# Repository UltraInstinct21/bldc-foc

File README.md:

# bldc-foc

Sensored field-oriented control firmware for a custom 24 V BLDC drive:

- STM32G431CBT6 (170 MHz, LQFP-48)
- DRV8316CT gate driver, 6x PWM in hardware mode, integrated current sense (0.3 V/A)
- AS5600 magnetic encoder on I2C1
- 24 V outrunner, 7 pole pairs, 5 Arms, 2000 rpm
- External ESP32 WiFi bridge for browser-based telemetry and motor control

The firmware is split into independent test applications, one per board
function, plus standalone FOC and FOC + ESP32 WiFi bridge applications. Each app
links the same board layer and is flashed on its own.

## Layout

| Path | Contents |
|---|---|
| `firmware/` | Build system and STM32 source code |
| `firmware/common/` | Clock, GPIO, pin AFs, interrupts, UART console & link |
| `firmware/foc/` | Standalone FOC application (I2C encoder, automatic start) |
| `firmware/foc_esp/` | FOC application with ESP32 half-duplex UART link |
| `firmware/tests/` | Eight independent hardware test apps (`test_00` to `test_07`) |
| `firmware/Drivers/` | ST HAL and CMSIS |
| `esp32/` | Arduino sketch and web app for external ESP32 WiFi bridge |
| `hardware/` | KiCad schematic and PCB for board revision v6 |
| `docs/` | Hardware, motor, control, bring-up, and ESP32 interface documentation |

## Quick start

### STM32 firmware
Requirements: `arm-none-eabi-gcc`, OpenOCD, and an ST-Link probe.

```sh
cd firmware

make APP=test_00_hello flash    # first board check
make APP=test_07_esp_link flash # verify ESP32 link without motor
make APP=foc flash              # standalone FOC app
make APP=foc_esp flash          # FOC + ESP32 WiFi control app
make apps                       # build every app
```

Full build and flash details are in [`firmware/README.md`](firmware/README.md).

### ESP32 WiFi bridge
Flash `esp32/bldc_bridge/bldc_bridge.ino` using the Arduino IDE.
Connect to WiFi **BLDC-FOC** (password `bldcfoc123`) and open `http://192.168.4.1`.
See [`esp32/README.md`](esp32/README.md) for wiring and setup.

## Documentation

- [`docs/hardware.md`](docs/hardware.md) - board, pin map, connectors, limitations
- [`docs/motor.md`](docs/motor.md) - motor data and the constants derived from it
- [`docs/control.md`](docs/control.md) - FOC implementation, tuning, sampling window
- [`docs/bringup.md`](docs/bringup.md) - ordered test and calibration procedure
- [`docs/esp32.md`](docs/esp32.md) - ESP32 WiFi bridge protocol, timing, and safety design
- [`firmware/tests/README.md`](firmware/tests/README.md) - expected output per test
- [`firmware/foc_esp/README.md`](firmware/foc_esp/README.md) - FOC + ESP32 application details
- [`esp32/README.md`](esp32/README.md) - ESP32 Arduino build, flash, and wiring guide
- [`hardware/README.md`](hardware/README.md) - PCB files and board notes

## Current state

- Current-mode FOC at 20 kHz, angle from the AS5600.
- Standalone `foc`: ramps a fixed `iq` and guards at 800 rpm.
- WiFi-controlled `foc_esp`: commanded over half-duplex UART at 230400 baud with dual watchdogs.
- The AS5600 is a bring-up sensor (about 1000 rpm max). Rated speed needs an ABZ
  or SPI absolute encoder.
- The board has no Vbus sense; the 0.3 V/A CSA gain limits measurable current to ±4.6 A.

## License

MIT. See [`LICENSE`](LICENSE).

The bundled ST HAL and CMSIS sources under `firmware/Drivers/` keep their own
ST license terms; see `firmware/Drivers/CMSIS/LICENSE.txt` and the headers in
the HAL sources.

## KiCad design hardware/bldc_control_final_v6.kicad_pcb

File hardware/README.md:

# BLDC Motor Controller — Board Revision v6

KiCad sources for the 24 V three-phase BLDC drive, board revision v6
(`bldc_control_final_v6`).

| File | Contents |
|---|---|
| `bldc_control_final_v6.kicad_pro` | KiCad project |
| `bldc_control_final_v6.kicad_sch` | Single-sheet schematic |
| `bldc_control_final_v6.kicad_pcb` | 2-layer PCB |

Open the `.kicad_pro` file with KiCad 7 or newer.

## Quick facts

| Item | Value |
|---|---|
| Input voltage | 12 to 24 V DC on J1; USB-C 5 V as alternate supply |
| Motor output | Three phases on J2 (ph_C, ph_B, ph_A) |
| Gate driver | DRV8316CT, integrated FETs, 6x PWM, hardware strap configuration, no SPI |
| Current sense | Integrated CSA, 0.3 V/A, VREF = 3.3 V, linear range ±4.6 A |
| MCU | STM32G431CBT6, LQFP-48, 170 MHz, 128 KB flash, 32 KB RAM |
| Power regulators | LMR36510 buck (24 V → 5 V), TPS2116 mux, TPS7A4533 LDO (5 V → 3.3 V) |
| Encoder interface | I2C1 on PA15 (SCL) and PB7 (SDA), J6 / J7 |
| Debug / link | USART1 on J7 (PB6 TX, PB7 RX) |
| Programming | SWD on J5 |
| PCB | 2-layer, Rev v6 |

## Connectors

| Connector | Pins | Signal | Description |
|---|---|---|---|
| J1 | 2 | 12–24 V / GND | Motor supply input |
| J2 | 3 | ph_C / ph_B / ph_A | Motor phase outputs |
| J3 | — | USB-C | 5 V backup supply and USB data (see errata) |
| J5 | 4 | 3V3 / SWDIO / SWCLK / GND | SWD debug header |
| J6 | 3 | 3V3 / OUT (PA15) / GND | Encoder supply and SCL; also OUT pin |
| J7 | 2 | PB6 (USART1_TX) / PB7 (USART1_RX) | UART console and ESP32 link |

J7 has no ground pin. Use J5 pin 4 or J6 pin 3 as the signal ground.
J6 pin 2 connects to PA15, which carries I2C1_SCL (AF4) for the AS5600.

## Power tree

```
12–24 V input (J1)
    └── F1 PTC fuse
        └── LMR36510 buck  →  5 V
                               └── TPS2116 mux  ←  USB-C 5 V (J3)
                                       └── TPS7A4533 LDO  →  3.3 V
```

The DRV8316CT runs directly from the protected input rail. The STM32 and all
logic run from the 3.3 V LDO output.

## DRV8316CT hardware straps

The DRV8316CT is configured entirely by pin straps. There is no SPI connection
to the driver; the firmware only drives nSLEEP and DRVOFF and reads nFAULT.

| Pin | Strap | Setting | Result |
|---|---|---|---|
| MODE | AGND | — | 6x PWM mode, SOA/SOB/SOC outputs active |
| GAIN | Hi-Z | — | CSA gain 0.3 V/A |
| SLEW | 47 kΩ to AVDD | — | Gate slew rate 125 V/µs |
| OCP/SR | Hi-Z | — | OCP threshold 16 A, active demagnetization |
| VREF/ILIM | 3V3 | — | 1.65 V mid-rail offset, ±4.6 A linear CSA range |

## Known deviations and errata

| # | Item | Impact |
|---|---|---|
| 1 | USB-C CC pull-ups are connected to 3.3 V instead of 5.1 kΩ to GND | USB-C power negotiation fails; the board accepts 5 V but cannot negotiate higher current from a compliant charger |
| 2 | F1 PTC fuse is rated 16 V; input may reach 24 V | The fuse may trip at high current on a 24 V supply; verify thermal behaviour before sustained 24 V operation |
| 3 | SW4 connects NRST to 3.3 V instead of GND | Pressing SW4 has no effect; use the OpenOCD `reset` command or the SWD reset line to reset the MCU |
| 4 | BOOT0 is unconnected; it floats to logic 0 via the internal pull-down | The MCU always boots from flash; DFU mode via BOOT0 is not accessible without a hardware rework |
| 5 | DRV8316CT internal buck (SW_BK / FB_BK) is unused | Only an RC network is fitted; the internal buck is disabled. No functional impact |
| 6 | PB10 and PB11 are labelled I2C1_SCL / I2C1_SDA on the schematic | PB10/PB11 have no I2C1 alternate function on the STM32G431CB. The pads are unconnected on the board; do not use them for the encoder |
| 7 | CSA linear range is ±4.6 A; rated motor current is 7 A | Full motor torque cannot be measured accurately. Keep peak iq ≤ 4.0 A in firmware to stay within the measurement window |
| 8 | SLEW strap gives 125 V/µs (not 200 V/µs) | Dead-time margin is slightly reduced relative to the datasheet default. Keep `FOC_VMAX_FRAC` ≤ 0.45 in firmware |

## Firmware

The firmware build system and all source code are in `firmware/`. See
`../firmware/README.md` for build instructions, the application list, and
toolchain requirements.

The `foc_esp` application adds a half-duplex UART link to an external ESP32
WiFi bridge. See `../firmware/foc_esp/README.md` and `../docs/esp32.md`.

## Not in this repository

Schematic and PCB PDFs, Gerbers, drill files, the BOM and the motor design
report are kept locally and are covered by `.gitignore`.

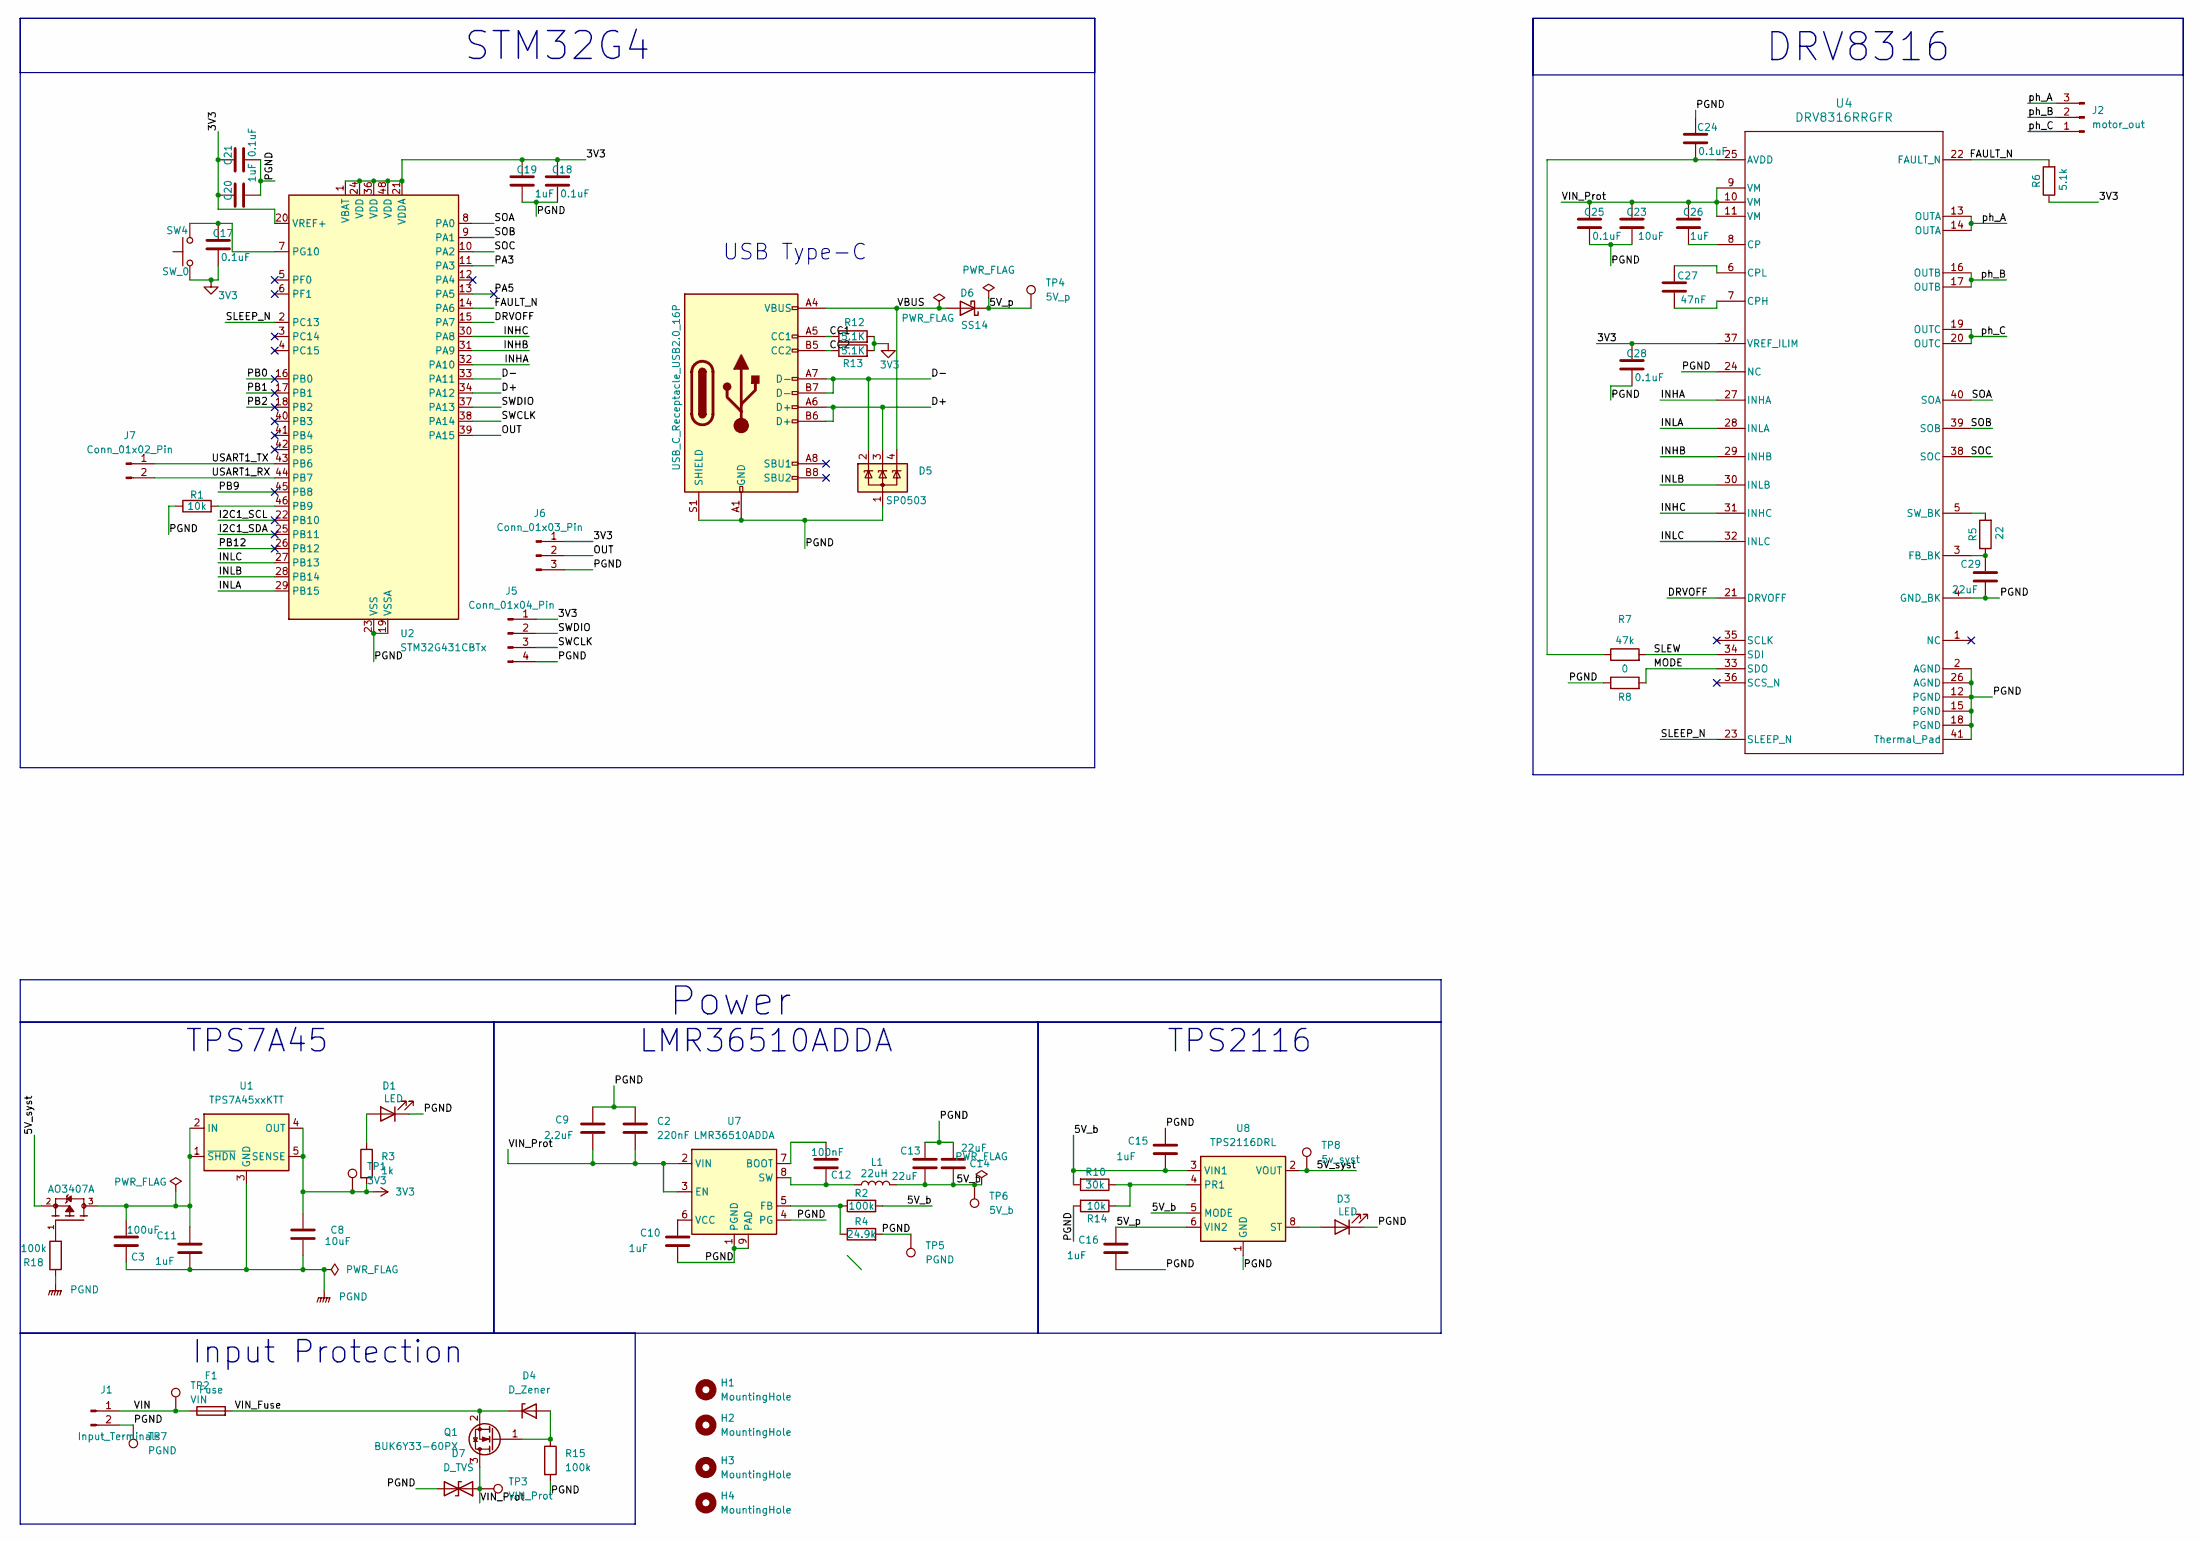
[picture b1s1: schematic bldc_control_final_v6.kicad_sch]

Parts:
C2: 220nF; C_0805_2012Metric_Pad1.18x1.45mm_HandSolder
C3: 100uF; C_0805_2012Metric_Pad1.18x1.45mm_HandSolder
C8: 10uF; C_0805_2012Metric_Pad1.18x1.45mm_HandSolder
C9: 2.2uF; C_0805_2012Metric_Pad1.18x1.45mm_HandSolder
C10, C11, C15, C16, C19, C20, C26: 1uF; C_0805_2012Metric_Pad1.18x1.45mm_HandSolder
C12: 100nF; C_0805_2012Metric_Pad1.18x1.45mm_HandSolder
C13, C14, C29: 22uF; C_1206_3216Metric_Pad1.33x1.80mm_HandSolder
C17, C18, C21, C24, C25, C28: 0.1uF; C_0805_2012Metric_Pad1.18x1.45mm_HandSolder
C23: 10uF; C_1210_3225Metric_Pad1.33x2.70mm_HandSolder
C27: 47nF; C_0805_2012Metric_Pad1.18x1.45mm_HandSolder
D1, D3: LED; LED_0603_1608Metric
D4: D_Zener; D_SOD-123
D5: SP0503; SOT-143
D6: SS14; D_SMA
D7: D_TVS; D_SMB_Handsoldering
F1: Fuse; Fuse_Bourns_MF-RHT500
H1, H2, H3, H4: MountingHole; MountingHole_2.2mm_M2
J1: Input_Terminals; TerminalBlock_Phoenix_PT-1,5-2-5.0-H_1x02_P5.00mm_Horizontal
J2: motor_out; TerminalBlock_Phoenix_PT-1,5-3-5.0-H_1x03_P5.00mm_Horizontal
J3: USB_C_Receptacle_USB2.0_16P; USB_C_Receptacle_GCT_USB4110
J5: Conn_01x04_Pin; PinHeader_1x04_P2.54mm_Vertical
J6: Conn_01x03_Pin; PinHeader_1x03_P2.54mm_Vertical
J7: Conn_01x02_Pin; PinHeader_1x02_P2.54mm_Vertical
L1: 22uH; L_Bourns-SRN6028
Q1: BUK6Y33-60PX; LFPAK56
Q2: AO3407A; SOT-23; PARTREV 5
R1, R14: 10k; R_0805_2012Metric_Pad1.20x1.40mm_HandSolder
R2, R15, R18: 100k; R_0805_2012Metric_Pad1.20x1.40mm_HandSolder
R3: 1k; R_0805_2012Metric_Pad1.20x1.40mm_HandSolder
R4: 24.9k; R_0805_2012Metric_Pad1.20x1.40mm_HandSolder
R5: 22; R_0805_2012Metric_Pad1.20x1.40mm_HandSolder
R6: 5.1k; R_0805_2012Metric_Pad1.20x1.40mm_HandSolder
R7: 47k; R_0805_2012Metric_Pad1.20x1.40mm_HandSolder
R8: 0; R_0805_2012Metric_Pad1.20x1.40mm_HandSolder
R10: 30k; R_0805_2012Metric_Pad1.20x1.40mm_HandSolder
R12, R13: 5.1K; R_0805_2012Metric_Pad1.20x1.40mm_HandSolder
SW4: SW_0; SW_Push_SPST_NO_Alps_SKRK
TP1: 3V3; TestPoint_Pad_1.5x1.5mm
TP2: VIN; TestPoint_Pad_1.5x1.5mm
TP3: VIN_Prot; TestPoint_Pad_1.5x1.5mm
TP4: 5V_p; TestPoint_Pad_1.5x1.5mm
TP5, TP7: PGND; TestPoint_Pad_1.5x1.5mm
TP6: 5V_b; TestPoint_Pad_1.5x1.5mm
TP8: 5v_syst; TestPoint_Pad_1.5x1.5mm
U1: TPS7A45xxKTT; SOT-223-6_TabPin3
U2: STM32G431CBTx; LQFP-48_7x7mm_P0.5mm
U4: DRV8316RRGFR; RGF0040E-IPC_A
U7: LMR36510ADDA; Texas_HTSOP-8-1EP_3.9x4.9mm_P1.27mm_EP2.95x4.9mm_Mask2.4x3.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
U8: TPS2116DRL; SOT-583-8

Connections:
3V3: C8.1, C17.1, C18.2, C19.2, C20.2, C21.2, C28.2, J5.1, J6.1, R3.2, R6.1, R12.2, R13.2, SW4.1, TP1.1 (1_1), U1.4 (OUT), U1.5 (SENSE), U2.1 (VBAT), U2.20 (VREF+), U2.21 (VDDA), U2.24 (VDD), U2.36 (VDD), U2.48 (VDD), U4.37 (VREF_ILIM); also elsewhere on the board
/5V_b: C13.2, C14.2, C15.2, L1.2, R2.2, R10.2, TP6.1 (1_1), U8.3 (VIN1), U8.5 (MODE); also elsewhere on the board
/5V_p: C16.1, D6.1 (K), TP4.1 (1_1), U8.6 (VIN2); also elsewhere on the board
/5V_syst: Q2.2, TP8.1 (1_1), U8.2 (VOUT), U8.7 (VOUT); also elsewhere on the board
/CC1: J3.A5 (CC1), R12.1
/CC2: J3.B5 (CC2), R13.1
/D+: D5.3 (K), J3.A6 (D+), J3.B6 (D+), U2.34 (PA12); also elsewhere on the board
/D-: D5.2 (K), J3.A7 (D-), J3.B7 (D-), U2.33 (PA11); also elsewhere on the board
/FAULT_N: R6.2, U2.14 (PA6), U4.22 (FAULT_N); also elsewhere on the board
/MODE: R8.2, U4.33 (SDO); also elsewhere on the board
/OUT: J6.2, U2.39 (PA15); also elsewhere on the board
/SLEW: R7.2, U4.34 (SDI); also elsewhere on the board
/SWCLK: J5.3, U2.38 (PA14); also elsewhere on the board
/SWDIO: J5.2, U2.37 (PA13); also elsewhere on the board
/USART1_RX: J7.2, U2.44 (PB7); also elsewhere on the board
/USART1_TX: J7.1, U2.43 (PB6); also elsewhere on the board
/VBUS: D5.4 (K), D6.2 (A), J3.A4 (VBUS), J3.A9 (VBUS), J3.B4 (VBUS), J3.B9 (VBUS)
/VIN: F1.1, J1.1, TP2.1 (1_1)
/VIN_Fuse: D4.1 (K), F1.2, Q1.2 (S)
/VIN_Prot: C2.2, C9.2, C23.2, C25.2, C26.2, D7.1 (A1), Q1.3 (D), TP3.1 (1_1), U4.9 (VM), U4.10 (VM), U4.11 (VM), U7.2 (VIN), U7.3 (EN); also elsewhere on the board
/ph_A: J2.3, U4.13 (OUTA), U4.14 (OUTA); also elsewhere on the board
/ph_B: J2.2, U4.16 (OUTB), U4.17 (OUTB); also elsewhere on the board
/ph_C: J2.1, U4.19 (OUTC), U4.20 (OUTC); also elsewhere on the board
unnamed: D1.2 (A), R3.1
unnamed 44: D3.2 (A), U8.8 (ST); also elsewhere on the board
unnamed: D4.2 (A), Q1.1 (G), R15.1
unnamed: Q2.1, R18.2
unnamed 47: C3.1, C11.1, Q2.3, U1.1 (~SHDN), U1.2 (IN); also elsewhere on the board
unnamed 48: R1.2, U2.46 (PB9); also elsewhere on the board
unnamed 49: C17.2, SW4.2, U2.7 (PG10); also elsewhere on the board
unnamed: U2.2 (PC13), U4.23 (SLEEP_N)
unnamed: U2.8 (PA0), U4.40 (SOA)
unnamed: U2.9 (PA1), U4.39 (SOB)
unnamed: U2.10 (PA2), U4.38 (SOC)
unnamed: U2.15 (PA7), U4.21 (DRVOFF)
unnamed: U2.27 (PB13), U4.32 (INLC)
unnamed: U2.28 (PB14), U4.30 (INLB)
unnamed: U2.29 (PB15), U4.28 (INLA)
unnamed: U2.30 (PA8), U4.31 (INHC)
unnamed: U2.31 (PA9), U4.29 (INHB)
unnamed: U2.32 (PA10), U4.27 (INHA)
unnamed 61: C24.1, R7.1, U4.25 (AVDD); also elsewhere on the board
unnamed 62: C26.1, U4.8 (CP); also elsewhere on the board
unnamed 63: C27.1, U4.7 (CPH); also elsewhere on the board
unnamed 64: C27.2, U4.6 (CPL); also elsewhere on the board
unnamed 65: C29.1, R5.1, U4.3 (FB_BK); also elsewhere on the board
unnamed 66: R5.2, U4.5 (SW_BK); also elsewhere on the board
unnamed 67: C12.1, U7.7 (BOOT); also elsewhere on the board
unnamed 68: R2.1, R4.1, U7.5 (FB); also elsewhere on the board
unnamed 69: C12.2, L1.1, U7.8 (SW); also elsewhere on the board
unnamed 70: C10.1, U7.6 (VCC); also elsewhere on the board
unnamed 71: R10.1, R14.1, U8.4 (PR1); also elsewhere on the board
PGND: C2.1, C3.2, C8.2, C9.1, C10.2, C11.2, C13.1, C14.1, C15.1, C16.2, C18.1, C19.1, C20.1, C21.1, C23.1, C24.2, C25.1, C28.1, C29.2, D1.1 (K), D3.1 (K), D5.1 (A), D7.2 (A2), J1.2, J3.A1 (GND), J3.A12 (GND), J3.B1 (GND), J3.B12 (GND), J3.S1 (SHIELD), J5.4, J6.3, R1.1, R4.2, R8.1, R14.2, R15.2, R18.1, TP5.1 (1_1), TP7.1 (1_1), U1.3 (GND), U2.19 (VSSA), U2.23 (VSS), U2.35 (VSS), U2.47 (VSS), U4.2 (AGND), U4.4 (GND_BK), U4.12 (PGND), U4.15 (PGND), U4.18 (PGND), U4.24 (NC), U4.26 (AGND), U4.41 (Thermal_Pad), U7.1 (PGND), U7.4 (PG), U7.9 (PAD), U8.1 (GND); also elsewhere on the board

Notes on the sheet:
USB Type-C
LMR36510ADDA
TPS7A45
TPS2116
Power
DRV8316
STM32G4
Input Protection

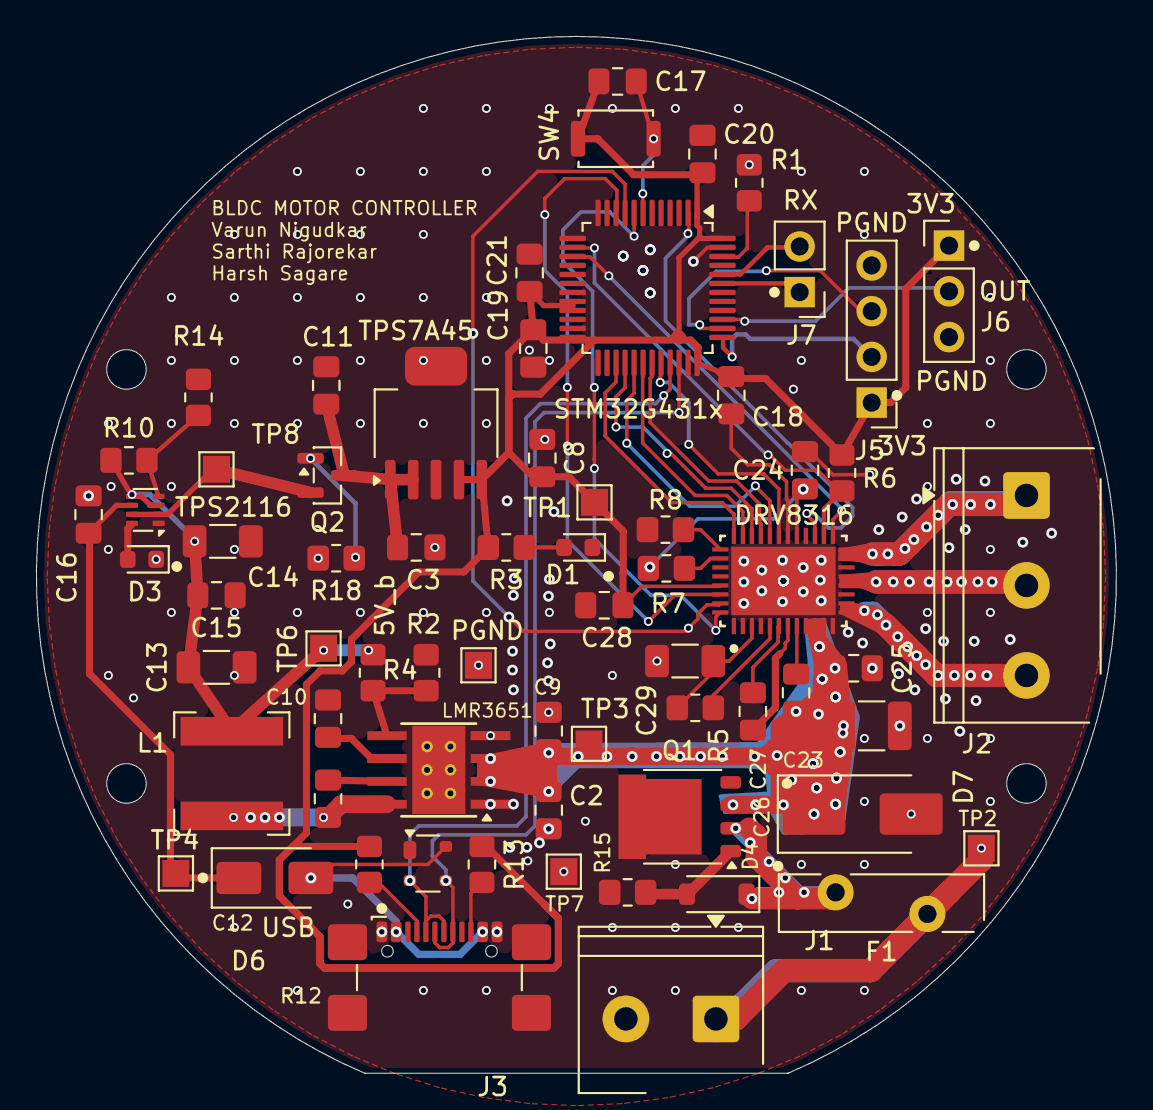
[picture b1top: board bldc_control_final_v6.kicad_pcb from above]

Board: 2 copper layers, 60.0 x 57.6 mm, 71 parts (0 on the bottom side), 53 nets.

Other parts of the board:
DRV8316: DRV8316RRGFR; RGF0040E-IPC_A
LMR3651: LMR36510ADDA; Texas_HTSOP-8-1EP_3.9x4.9mm_P1.27mm_EP2.95x4.9mm_Mask2.4x3.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
STM32G431x: STM32G431CBTx; LQFP-48_7x7mm_P0.5mm
TPS7A45: TPS7A45xxKTT; SOT-223-6_TabPin3
TPS2116: TPS2116DRL; SOT-583-8

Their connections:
3V3: DRV8316.37 (VREF_ILIM), STM32G431x.1 (VBAT), STM32G431x.20 (VREF+), STM32G431x.21 (VDDA), STM32G431x.24 (VDD), STM32G431x.36 (VDD), STM32G431x.48 (VDD), TPS7A45.4 (OUT), TPS7A45.5 (SENSE); also elsewhere on the board
/5V_b: TPS2116.3 (VIN1), TPS2116.5 (MODE); also elsewhere on the board
/5V_p: TPS2116.6 (VIN2); also elsewhere on the board
/5V_syst: TPS2116.2 (VOUT), TPS2116.7 (VOUT); also elsewhere on the board
/D+: STM32G431x.34 (PA12); also elsewhere on the board
/D-: STM32G431x.33 (PA11); also elsewhere on the board
/DRVOFF: DRV8316.21 (DRVOFF), STM32G431x.15 (PA7)
/FAULT_N: DRV8316.22 (FAULT_N), STM32G431x.14 (PA6); also elsewhere on the board
/INHA: DRV8316.27 (INHA), STM32G431x.32 (PA10)
/INHB: DRV8316.29 (INHB), STM32G431x.31 (PA9)
/INHC: DRV8316.31 (INHC), STM32G431x.30 (PA8)
/INLA: DRV8316.28 (INLA), STM32G431x.29 (PB15)
/INLB: DRV8316.30 (INLB), STM32G431x.28 (PB14)
/INLC: DRV8316.32 (INLC), STM32G431x.27 (PB13)
/MODE: DRV8316.33 (SDO); also elsewhere on the board
/OUT: STM32G431x.39 (PA15); also elsewhere on the board
/SLEEP_N: DRV8316.23 (SLEEP_N), STM32G431x.2 (PC13)
/SLEW: DRV8316.34 (SDI); also elsewhere on the board
/SOA: DRV8316.40 (SOA), STM32G431x.8 (PA0)
/SOB: DRV8316.39 (SOB), STM32G431x.9 (PA1)
/SOC: DRV8316.38 (SOC), STM32G431x.10 (PA2)
/SWCLK: STM32G431x.38 (PA14); also elsewhere on the board
/SWDIO: STM32G431x.37 (PA13); also elsewhere on the board
/USART1_RX: STM32G431x.44 (PB7); also elsewhere on the board
/USART1_TX: STM32G431x.43 (PB6); also elsewhere on the board
/VIN_Prot: DRV8316.9 (VM), DRV8316.10 (VM), DRV8316.11 (VM), LMR3651.2 (VIN), LMR3651.3 (EN); also elsewhere on the board
/ph_A: DRV8316.13 (OUTA), DRV8316.14 (OUTA); also elsewhere on the board
/ph_B: DRV8316.16 (OUTB), DRV8316.17 (OUTB); also elsewhere on the board
/ph_C: DRV8316.19 (OUTC), DRV8316.20 (OUTC); also elsewhere on the board
unnamed 44: TPS2116.8 (ST); also elsewhere on the board
unnamed 47: TPS7A45.1 (~SHDN), TPS7A45.2 (IN); also elsewhere on the board
unnamed 48: STM32G431x.46 (PB9); also elsewhere on the board
unnamed 49: STM32G431x.7 (PG10); also elsewhere on the board
unnamed 61: DRV8316.25 (AVDD); also elsewhere on the board
unnamed 62: DRV8316.8 (CP); also elsewhere on the board
unnamed 63: DRV8316.7 (CPH); also elsewhere on the board
unnamed 64: DRV8316.6 (CPL); also elsewhere on the board
unnamed 65: DRV8316.3 (FB_BK); also elsewhere on the board
unnamed 66: DRV8316.5 (SW_BK); also elsewhere on the board
unnamed 67: LMR3651.7 (BOOT); also elsewhere on the board
unnamed 68: LMR3651.5 (FB); also elsewhere on the board
unnamed 69: LMR3651.8 (SW); also elsewhere on the board
unnamed 70: LMR3651.6 (VCC); also elsewhere on the board
unnamed 71: TPS2116.4 (PR1); also elsewhere on the board
PGND: DRV8316.2 (AGND), DRV8316.4 (GND_BK), DRV8316.12 (PGND), DRV8316.15 (PGND), DRV8316.18 (PGND), DRV8316.24 (NC), DRV8316.26 (AGND), DRV8316.41 (Thermal_Pad), LMR3651.1 (PGND), LMR3651.4 (PG), LMR3651.9 (PAD), STM32G431x.19 (VSSA), STM32G431x.23 (VSS), STM32G431x.35 (VSS), STM32G431x.47 (VSS), TPS7A45.3 (GND), TPS2116.1 (GND); also elsewhere on the board

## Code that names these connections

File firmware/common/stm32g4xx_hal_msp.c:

/**
 * @file    stm32g4xx_hal_msp.c
 * @brief   Low-level clocks / pin AFs for bldc_control_final_v6.
 *
 * Pin map (verified against bldc_control_final_v6.kicad_pcb):
 *
 *   USART1_TX  PB6  AF7   J7.1  (debug console / ESP32 link)
 *   I2C1_SCL   PA15 AF4   J6.2  (AS5600)
 *   I2C1_SDA   PB7  AF4   J7.2  (AS5600, shares USART1_RX)
 *   TIM1_CH1   PA8  AF6 -> INHC
 *   TIM1_CH2   PA9  AF6 -> INHB
 *   TIM1_CH3   PA10 AF6 -> INHA
 *   TIM1_CH1N  PB13 AF6 -> INLC
 *   TIM1_CH2N  PB14 AF6 -> INLB
 *   TIM1_CH3N  PB15 AF4 -> INLA
 *   ADC1_IN1/2/3  PA0/PA1/PA2   SOA/SOB/SOC
 *
 * The DRV8316CT is strapped for hardware mode, so there is no SPI pin map.
 */
#include "board.h"

void HAL_MspInit(void)
{
    __HAL_RCC_SYSCFG_CLK_ENABLE();
    __HAL_RCC_PWR_CLK_ENABLE();
    HAL_PWREx_DisableUCPDDeadBattery();
}

void HAL_ADC_MspInit(ADC_HandleTypeDef *hadc)
{
    GPIO_InitTypeDef        gpio = {0};
    RCC_PeriphCLKInitTypeDef clk = {0};

    if (hadc->Instance != ADC1)
    {
        return;
    }

    clk.PeriphClockSelection = RCC_PERIPHCLK_ADC12;
    clk.Adc12ClockSelection  = RCC_ADC12CLKSOURCE_SYSCLK;
    if (HAL_RCCEx_PeriphCLKConfig(&clk) != HAL_OK)
    {
        Error_Handler();
    }

    __HAL_RCC_ADC12_CLK_ENABLE();
    __HAL_RCC_GPIOA_CLK_ENABLE();
    __HAL_RCC_DMAMUX1_CLK_ENABLE();
    __HAL_RCC_DMA1_CLK_ENABLE();

    /* PA0 = SOA, PA1 = SOB, PA2 = SOC */
    gpio.Pin  = GPIO_PIN_0 | GPIO_PIN_1 | GPIO_PIN_2;
    gpio.Mode = GPIO_MODE_ANALOG;
    gpio.Pull = GPIO_NOPULL;
    HAL_GPIO_Init(GPIOA, &gpio);

    hdma_adc1.Instance                 = DMA1_Channel1;
    hdma_adc1.Init.Request             = DMA_REQUEST_ADC1;
    hdma_adc1.Init.Direction           = DMA_PERIPH_TO_MEMORY;
    hdma_adc1.Init.PeriphInc           = DMA_PINC_DISABLE;
    hdma_adc1.Init.MemInc              = DMA_MINC_ENABLE;
    hdma_adc1.Init.PeriphDataAlignment = DMA_PDATAALIGN_HALFWORD;
    hdma_adc1.Init.MemDataAlignment    = DMA_MDATAALIGN_HALFWORD;
    hdma_adc1.Init.Mode                = DMA_CIRCULAR;
    hdma_adc1.Init.Priority            = DMA_PRIORITY_HIGH;
    if (HAL_DMA_Init(&hdma_adc1) != HAL_OK)
    {
        Error_Handler();
    }
    __HAL_LINKDMA(hadc, DMA_Handle, hdma_adc1);

    HAL_NVIC_SetPriority(DMA1_Channel1_IRQn, 1u, 0u);
    HAL_NVIC_EnableIRQ(DMA1_Channel1_IRQn);
}

void HAL_I2C_MspInit(I2C_HandleTypeDef *hi2c)
{
    GPIO_InitTypeDef        gpio = {0};
    RCC_PeriphCLKInitTypeDef clk = {0};

    if (hi2c->Instance != I2C1)
    {
        return;
    }

    clk.PeriphClockSelection = RCC_PERIPHCLK_I2C1;
    clk.I2c1ClockSelection   = RCC_I2C1CLKSOURCE_PCLK1;
    if (HAL_RCCEx_PeriphCLKConfig(&clk) != HAL_OK)
    {
        Error_Handler();
    }

    __HAL_RCC_GPIOA_CLK_ENABLE();
    __HAL_RCC_GPIOB_CLK_ENABLE();
    __HAL_RCC_I2C1_CLK_ENABLE();

    /* PA15 = SCL, PB7 = SDA. Open drain; external 4.7k pull-ups required. */
    gpio.Mode      = GPIO_MODE_AF_OD;
    gpio.Pull      = GPIO_NOPULL;
    gpio.Speed     = GPIO_SPEED_FREQ_VERY_HIGH;
    gpio.Alternate = GPIO_AF4_I2C1;

    gpio.Pin = GPIO_PIN_15;
    HAL_GPIO_Init(GPIOA, &gpio);
    gpio.Pin = GPIO_PIN_7;
    HAL_GPIO_Init(GPIOB, &gpio);

    HAL_NVIC_SetPriority(I2C1_EV_IRQn, 5u, 0u);
    HAL_NVIC_EnableIRQ(I2C1_EV_IRQn);
    HAL_NVIC_SetPriority(I2C1_ER_IRQn, 5u, 0u);
    HAL_NVIC_EnableIRQ(I2C1_ER_IRQn);
}

void HAL_TIM_Base_MspInit(TIM_HandleTypeDef *htim)
{
    if (htim->Instance == TIM1)
    {
        __HAL_RCC_TIM1_CLK_ENABLE();
    }
}

void HAL_TIM_PWM_MspInit(TIM_HandleTypeDef *htim)
{
    if (htim->Instance == TIM1)
    {
        __HAL_RCC_TIM1_CLK_ENABLE();
    }
}

void HAL_TIM_MspPostInit(TIM_HandleTypeDef *htim)
{
    GPIO_InitTypeDef gpio = {0};

    if (htim->Instance != TIM1)
    {
        return;
    }

    __HAL_RCC_GPIOA_CLK_ENABLE();
    __HAL_RCC_GPIOB_CLK_ENABLE();

    /* PA8/PA9/PA10 = CH1/CH2/CH3 (AF6). */
    gpio.Pin       = GPIO_PIN_8 | GPIO_PIN_9 | GPIO_PIN_10;
    gpio.Mode      = GPIO_MODE_AF_PP;
    gpio.Pull      = GPIO_NOPULL;
    gpio.Speed     = GPIO_SPEED_FREQ_VERY_HIGH;
    gpio.Alternate = GPIO_AF6_TIM1;
    HAL_GPIO_Init(GPIOA, &gpio);

    /* PB13/PB14 = CH1N/CH2N (AF6). */
    gpio.Pin = GPIO_PIN_13 | GPIO_PIN_14;
    HAL_GPIO_Init(GPIOB, &gpio);

    /* PB15 = CH3N is AF4 on this package. */
    gpio.Pin       = GPIO_PIN_15;
    gpio.Alternate = GPIO_AF4_TIM1;
    HAL_GPIO_Init(GPIOB, &gpio);
}

void HAL_UART_MspInit(UART_HandleTypeDef *huart)
{
    GPIO_InitTypeDef        gpio = {0};
    RCC_PeriphCLKInitTypeDef clk = {0};

    if (huart->Instance != USART1)
    {
        return;
    }

    clk.PeriphClockSelection = RCC_PERIPHCLK_USART1;
    clk.Usart1ClockSelection = RCC_USART1CLKSOURCE_PCLK2;
    if (HAL_RCCEx_PeriphCLKConfig(&clk) != HAL_OK)
    {
        Error_Handler();
    }

    __HAL_RCC_GPIOB_CLK_ENABLE();
    __HAL_RCC_USART1_CLK_ENABLE();

    /* TX only: PB6 AF7. PB7 is intentionally left to I2C1_SDA. */
    gpio.Pin       = GPIO_PIN_6;
    gpio.Mode      = GPIO_MODE_AF_PP;
    gpio.Pull      = GPIO_NOPULL;
    gpio.Speed     = GPIO_SPEED_FREQ_LOW;
    gpio.Alternate = GPIO_AF7_USART1;
    HAL_GPIO_Init(GPIOB, &gpio);
}

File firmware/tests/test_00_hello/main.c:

/**
 * @file    main.c
 * @brief   test_00_hello — power, clock, UART and GPIO smoke test.
 *
 * Covers the always-on part of the board:
 *   - 3V3 regulator and MCU boot
 *   - 170 MHz clock tree (HSI16 -> PLL)
 *   - USART1 TX on PB6 / J7.1 (115200 8N1)
 *   - nSLEEP / DRVOFF / nFAULT pin states (hardware strapped DRV8316CT)
 *
 * Expected UART output:
 *   banner, clock frequencies, UID, then a 1 Hz status line.
 *
 * No motor output is enabled. nSLEEP stays low and DRVOFF stays high.
 */
#include "board.h"
#include "debug.h"

int main(void)
{
    Board_Init();

    DBG_Puts("\r\n\r\n");
    DBG_Puts("==================================================\r\n");
    DBG_Puts(" bldc_control_final_v6  |  test_00_hello\r\n");
    DBG_Puts(" STM32G431CBT6 + DRV8316CT (Hardware Mode)\r\n");
    DBG_Puts("==================================================\r\n");

    DBG_Printf("build      : %s %s\r\n", __DATE__, __TIME__);
    DBG_Printf("SYSCLK     : %lu Hz\r\n", (unsigned long)HAL_RCC_GetSysClockFreq());
    DBG_Printf("HCLK       : %lu Hz\r\n", (unsigned long)HAL_RCC_GetHCLKFreq());
    DBG_Printf("PCLK1      : %lu Hz\r\n", (unsigned long)HAL_RCC_GetPCLK1Freq());
    DBG_Printf("PCLK2      : %lu Hz\r\n", (unsigned long)HAL_RCC_GetPCLK2Freq());
    DBG_Printf("UID        : %08lX-%08lX-%08lX\r\n",
               (unsigned long)HAL_GetUIDw0(),
               (unsigned long)HAL_GetUIDw1(),
               (unsigned long)HAL_GetUIDw2());

    DBG_Puts("\r\nControl pins:\r\n");
    DBG_Puts("  nSLEEP = PC13 [expected 0 = DRV asleep]\r\n");
    DBG_Puts("  DRVOFF = PA7  [expected 1 = outputs off]\r\n");
    DBG_Puts("  nFAULT = PA6  [expected 1 = no fault]\r\n");

    DBG_Puts("\r\nIf you can read this, power, clock and UART are good.\r\n");
    DBG_Puts("Status line follows once per second.\r\n\r\n");

    for (;;)
    {
        DBG_Printf("t=%6lu ms  nSLEEP=%u  DRVOFF=%u  nFAULT=%u\r\n",
                   (unsigned long)Board_Millis(),
                   (unsigned)HAL_GPIO_ReadPin(DRV_NSLEEP_PORT, DRV_NSLEEP_PIN),
                   (unsigned)HAL_GPIO_ReadPin(DRV_DRVOFF_PORT, DRV_DRVOFF_PIN),
                   (unsigned)HAL_GPIO_ReadPin(DRV_NFAULT_PORT, DRV_NFAULT_PIN));
        Board_DelayMs(1000u);
    }
}
